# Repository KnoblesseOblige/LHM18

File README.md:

# LHM18 Keyboard

  This is a Left Hand Mini 1800 style keyboard that was my first project to learn PCB design through KiCAD. The PCB design is based around a ProMicro and daughter board which uses USB mini-B similar to the [Tanuki Keyboard](https://github.com/SethSenpai/Tanuki). The PCB only supports the layout that is shown in the image above. Please feel free to modify the PCB or case files to fit your needs. 

 # Case

 The case is a typical top mounted desin with the intention for it to be 3D printed with the mounting solution being M2 heat-set inserts and screws. I sourced my hardware from McMaster-Carr:

 [M2 Heat-Set Insert](https://www.mcmaster.com/94180a307) qty 10

 [M2 Screws](https://www.mcmaster.com/92000a012) qty 10

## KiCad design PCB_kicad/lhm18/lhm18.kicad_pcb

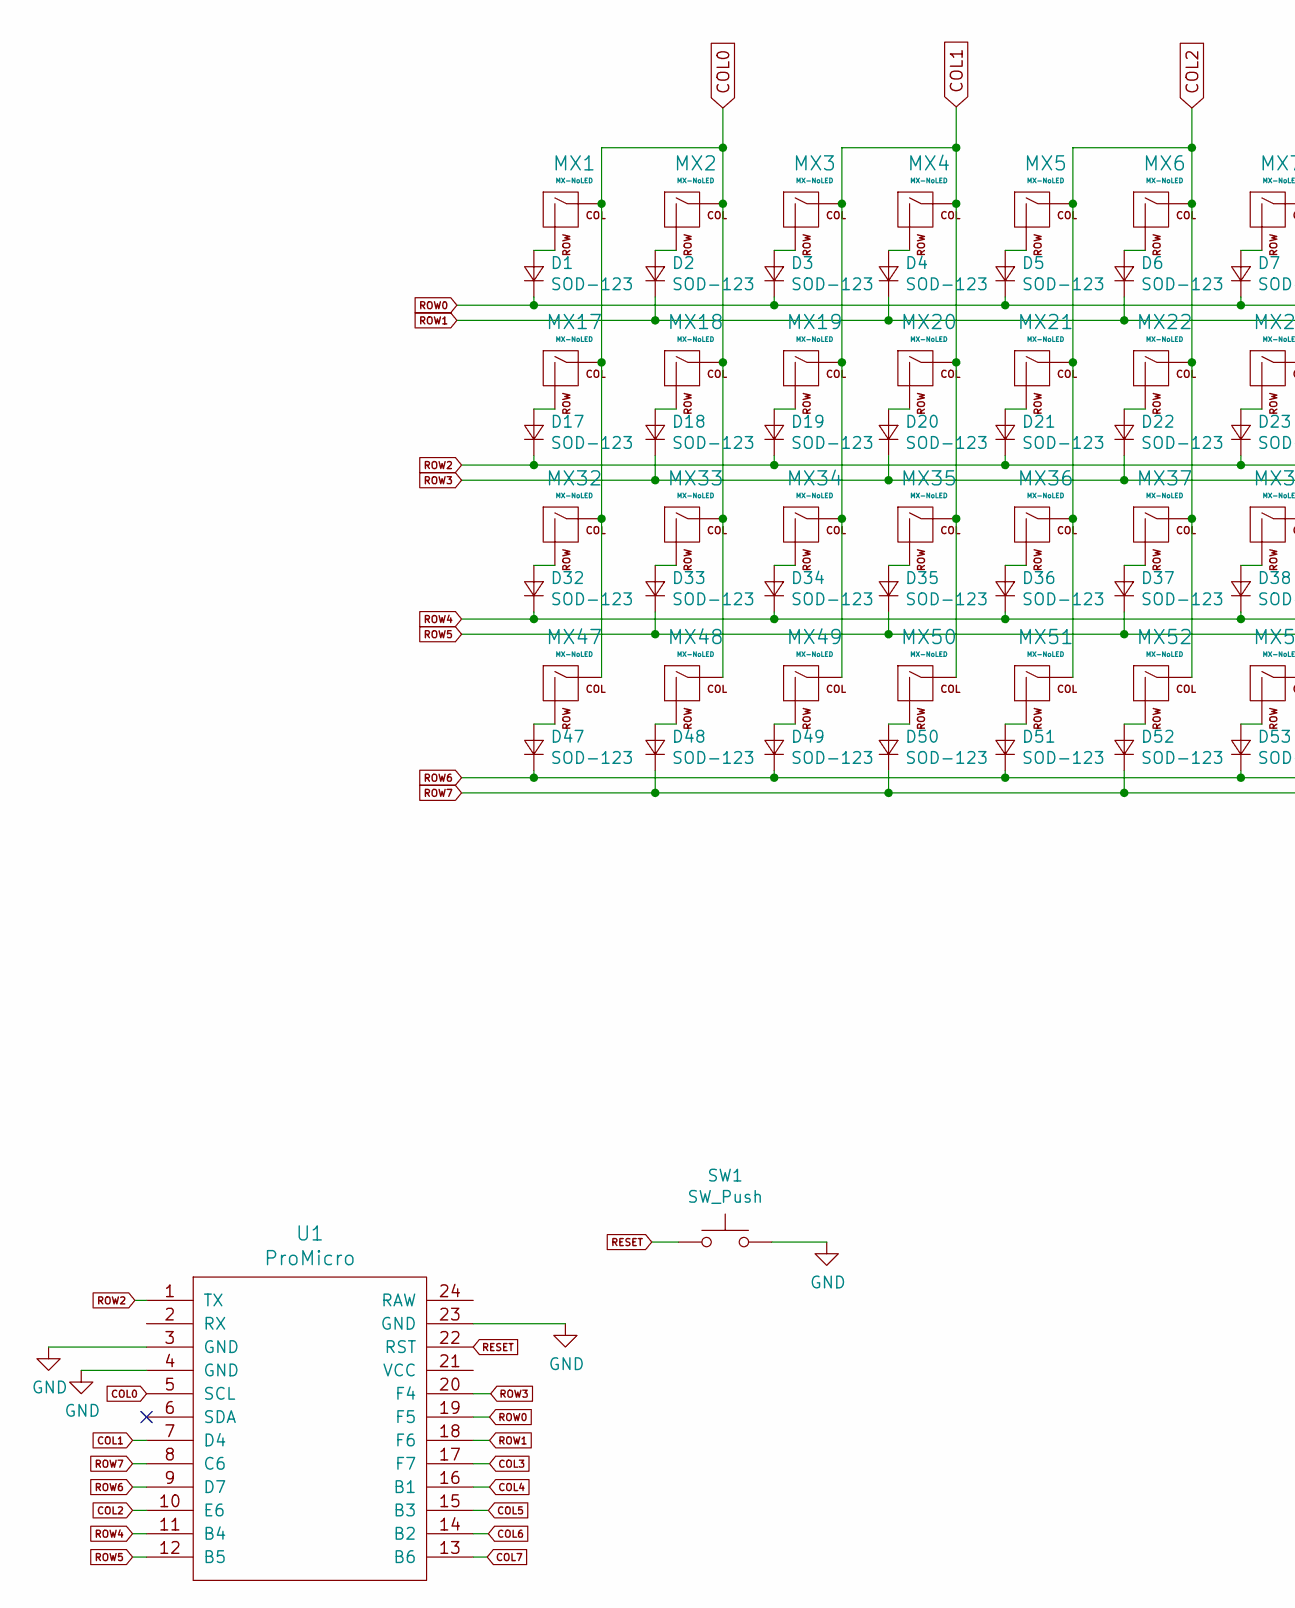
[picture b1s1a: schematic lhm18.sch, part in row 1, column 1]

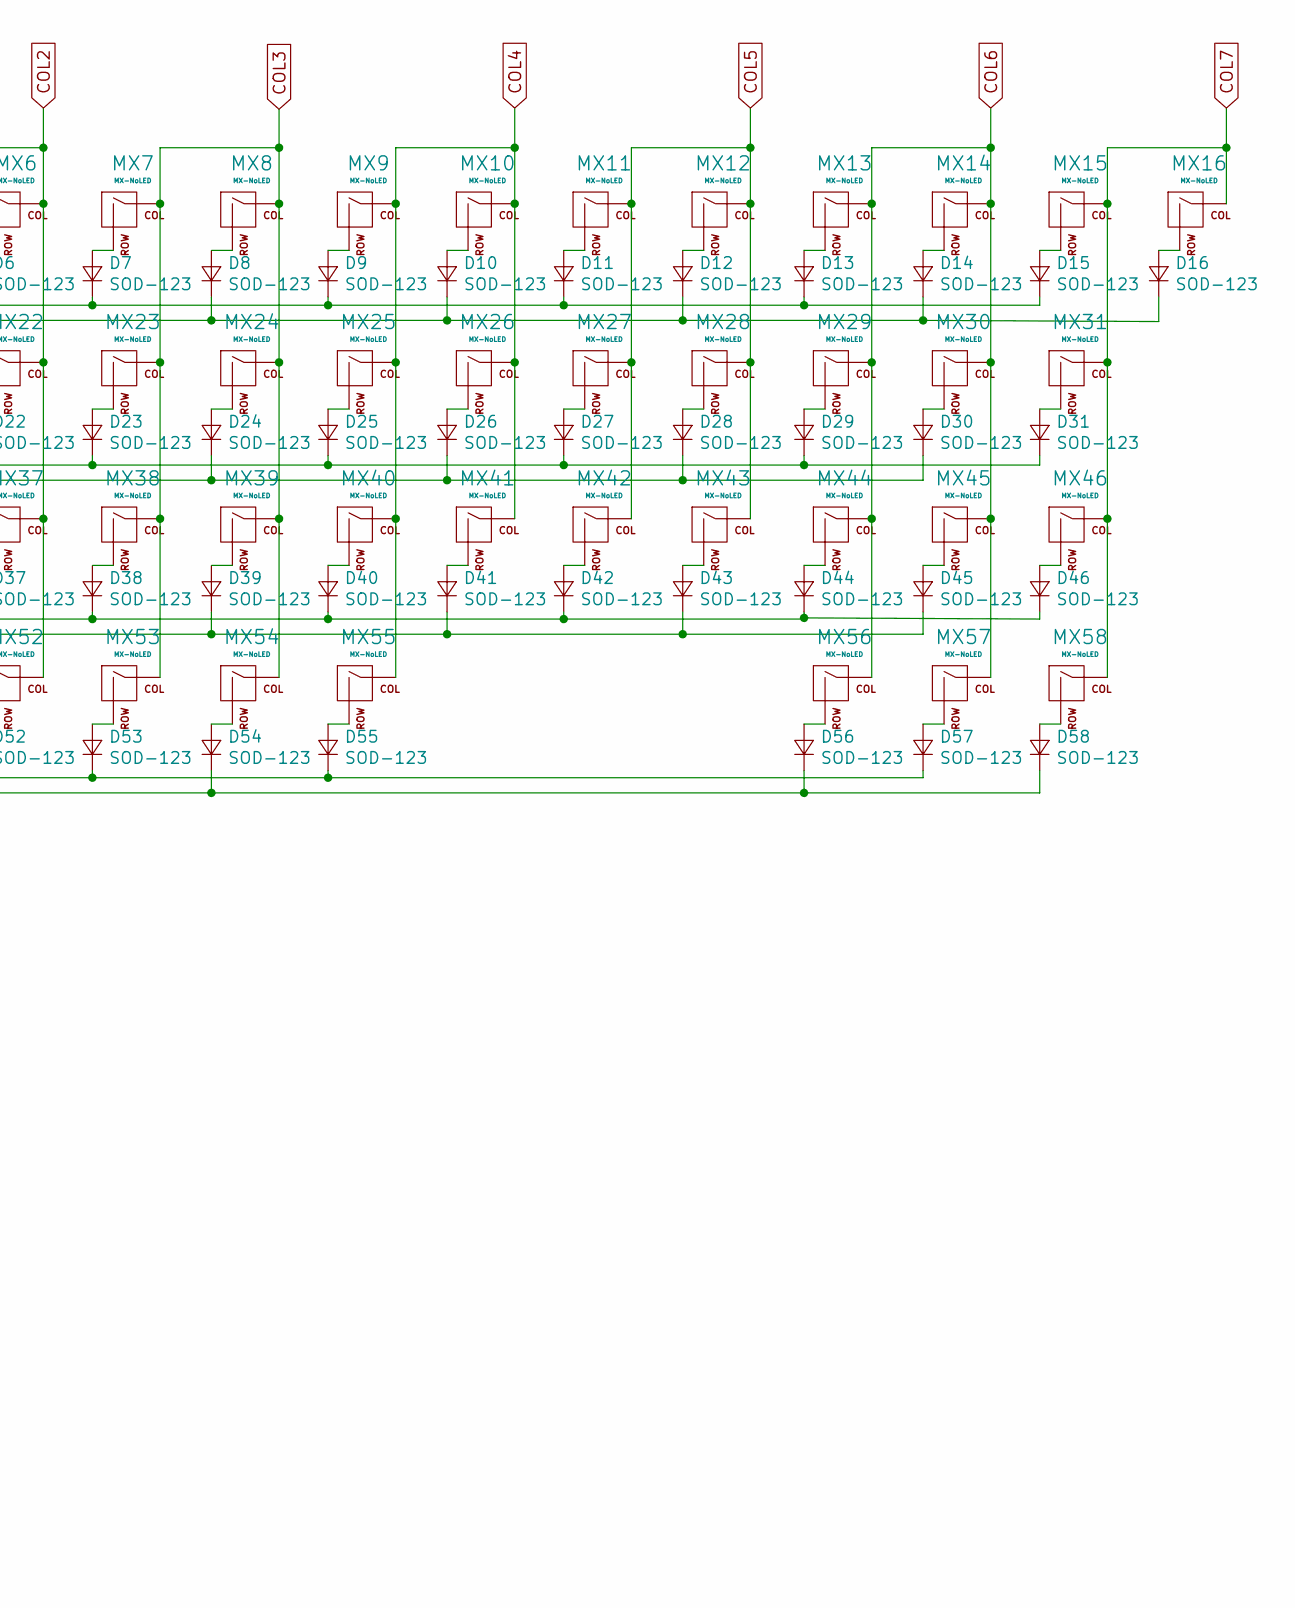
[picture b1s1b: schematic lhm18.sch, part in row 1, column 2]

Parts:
D1, D2, D3, D4, D5, D6, D7, D8, D9, D10, D11, D12, D13, D14, D15, D16, D17, D18, D19, D20, D21, D22, D23, D24, D25, D26, D27, D28, D29, D30, D31, D32, D33, D34, D35, D36, D37, D38, D39, D40, D41, D42, D43, D44, D45, D46, D47, D48, D49, D50, D51, D52, D53, D54, D55, D56, D57, D58: SOD-123; D_SOD123_axial
MX1, MX2, MX3, MX4, MX5, MX6, MX7, MX8, MX9, MX10, MX11, MX12, MX13, MX14, MX15, MX16, MX17, MX18, MX19, MX20, MX22, MX23, MX24, MX25, MX26, MX27, MX28, MX29, MX30, MX32, MX33, MX34, MX35, MX37, MX38, MX39, MX40, MX41, MX42, MX43, MX44, MX45, MX47, MX48, MX49, MX50, MX51, MX57: MX-NoLED; MXOnly-1U-NoLED
MX21, MX46, MX52, MX53, MX56, MX58: MX-NoLED; MXOnly-1.25U-NoLED
MX31, MX36: MX-NoLED; MXOnly-1.75U-NoLED
MX54: MX-NoLED; MXOnly-2.25U-ReversedStabilizers-NoLED
MX55: MX-NoLED; MXOnly-2.75U-ReversedStabilizers-NoLED
SW1: SW_Push; SKQG-1155865
U1: ProMicro

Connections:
COL0: MX1.1 (COL), MX2.1 (COL), MX17.1 (COL), MX18.1 (COL), MX32.1 (COL), MX33.1 (COL), MX47.1 (COL), MX48.1 (COL), U1.5 (SCL)
COL1: MX3.1 (COL), MX4.1 (COL), MX19.1 (COL), MX20.1 (COL), MX34.1 (COL), MX35.1 (COL), MX49.1 (COL), MX50.1 (COL), U1.7 (D4)
COL2: MX5.1 (COL), MX6.1 (COL), MX21.1 (COL), MX22.1 (COL), MX36.1 (COL), MX37.1 (COL), MX51.1 (COL), MX52.1 (COL), U1.10 (E6)
COL3: MX7.1 (COL), MX8.1 (COL), MX23.1 (COL), MX24.1 (COL), MX38.1 (COL), MX39.1 (COL), MX53.1 (COL), MX54.1 (COL), U1.17 (F7)
COL4: MX9.1 (COL), MX10.1 (COL), MX25.1 (COL), MX26.1 (COL), MX40.1 (COL), MX41.1 (COL), MX55.1 (COL), U1.16 (B1)
COL5: MX11.1 (COL), MX12.1 (COL), MX27.1 (COL), MX28.1 (COL), MX42.1 (COL), MX43.1 (COL), U1.15 (B3)
COL6: MX13.1 (COL), MX14.1 (COL), MX29.1 (COL), MX30.1 (COL), MX44.1 (COL), MX45.1 (COL), MX56.1 (COL), MX57.1 (COL), U1.14 (B2)
COL7: MX15.1 (COL), MX16.1 (COL), MX31.1 (COL), MX46.1 (COL), MX58.1 (COL), U1.13 (B6)
GND: SW1.2, U1.3 (GND), U1.4 (GND), U1.23 (GND)
unnamed: D1.2 (A), MX1.2 (ROW)
unnamed: D2.2 (A), MX2.2 (ROW)
unnamed: D3.2 (A), MX3.2 (ROW)
unnamed: D4.2 (A), MX4.2 (ROW)
unnamed: D5.2 (A), MX5.2 (ROW)
unnamed: D6.2 (A), MX6.2 (ROW)
unnamed: D7.2 (A), MX7.2 (ROW)
unnamed: D8.2 (A), MX8.2 (ROW)
unnamed: D9.2 (A), MX9.2 (ROW)
unnamed: D10.2 (A), MX10.2 (ROW)
unnamed: D11.2 (A), MX11.2 (ROW)
unnamed: D12.2 (A), MX12.2 (ROW)
unnamed: D13.2 (A), MX13.2 (ROW)
unnamed: D14.2 (A), MX14.2 (ROW)
unnamed: D15.2 (A), MX15.2 (ROW)
unnamed: D16.2 (A), MX16.2 (ROW)
unnamed: D17.2 (A), MX17.2 (ROW)
unnamed: D18.2 (A), MX18.2 (ROW)
unnamed: D19.2 (A), MX19.2 (ROW)
unnamed: D20.2 (A), MX20.2 (ROW)
unnamed: D21.2 (A), MX21.2 (ROW)
unnamed: D22.2 (A), MX22.2 (ROW)
unnamed: D23.2 (A), MX23.2 (ROW)
unnamed: D24.2 (A), MX24.2 (ROW)
unnamed: D25.2 (A), MX25.2 (ROW)
unnamed: D26.2 (A), MX26.2 (ROW)
unnamed: D27.2 (A), MX27.2 (ROW)
unnamed: D28.2 (A), MX28.2 (ROW)
unnamed: D29.2 (A), MX29.2 (ROW)
unnamed: D30.2 (A), MX30.2 (ROW)
unnamed: D31.2 (A), MX31.2 (ROW)
unnamed: D32.2 (A), MX32.2 (ROW)
unnamed: D33.2 (A), MX33.2 (ROW)
unnamed: D34.2 (A), MX34.2 (ROW)
unnamed: D35.2 (A), MX35.2 (ROW)
unnamed: D36.2 (A), MX36.2 (ROW)
unnamed: D37.2 (A), MX37.2 (ROW)
unnamed: D38.2 (A), MX38.2 (ROW)
unnamed: D39.2 (A), MX39.2 (ROW)
unnamed: D40.2 (A), MX40.2 (ROW)
unnamed: D41.2 (A), MX41.2 (ROW)
unnamed: D42.2 (A), MX42.2 (ROW)
unnamed: D43.2 (A), MX43.2 (ROW)
unnamed: D44.2 (A), MX44.2 (ROW)
unnamed: D45.2 (A), MX45.2 (ROW)
unnamed: D46.2 (A), MX46.2 (ROW)
unnamed: D47.2 (A), MX47.2 (ROW)
unnamed: D48.2 (A), MX48.2 (ROW)
unnamed: D49.2 (A), MX49.2 (ROW)
unnamed: D50.2 (A), MX50.2 (ROW)
unnamed: D51.2 (A), MX51.2 (ROW)
unnamed: D52.2 (A), MX52.2 (ROW)
unnamed: D53.2 (A), MX53.2 (ROW)
unnamed: D54.2 (A), MX54.2 (ROW)
unnamed: D55.2 (A), MX55.2 (ROW)
unnamed: D56.2 (A), MX56.2 (ROW)
unnamed: D57.2 (A), MX57.2 (ROW)
unnamed: D58.2 (A), MX58.2 (ROW)
RESET: SW1.1, U1.22 (RST)
RGB: U1.2 (RX)
ROW0: D1.1 (K), D3.1 (K), D5.1 (K), D7.1 (K), D9.1 (K), D11.1 (K), D13.1 (K), D15.1 (K), U1.19 (F5)
ROW1: D2.1 (K), D4.1 (K), D6.1 (K), D8.1 (K), D10.1 (K), D12.1 (K), D14.1 (K), D16.1 (K), U1.18 (F6)
ROW2: D17.1 (K), D19.1 (K), D21.1 (K), D23.1 (K), D25.1 (K), D27.1 (K), D29.1 (K), D31.1 (K), U1.1 (TX)
ROW3: D18.1 (K), D20.1 (K), D22.1 (K), D24.1 (K), D26.1 (K), D28.1 (K), D30.1 (K), U1.20 (F4)
ROW4: D32.1 (K), D34.1 (K), D36.1 (K), D38.1 (K), D40.1 (K), D42.1 (K), D44.1 (K), D46.1 (K), U1.11 (B4)
ROW5: D33.1 (K), D35.1 (K), D37.1 (K), D39.1 (K), D41.1 (K), D43.1 (K), D45.1 (K), U1.12 (B5)
ROW6: D47.1 (K), D49.1 (K), D51.1 (K), D53.1 (K), D55.1 (K), D57.1 (K), U1.9 (D7)
ROW7: D48.1 (K), D50.1 (K), D52.1 (K), D54.1 (K), D56.1 (K), D58.1 (K), U1.8 (C6)
VCC: U1.21 (VCC)

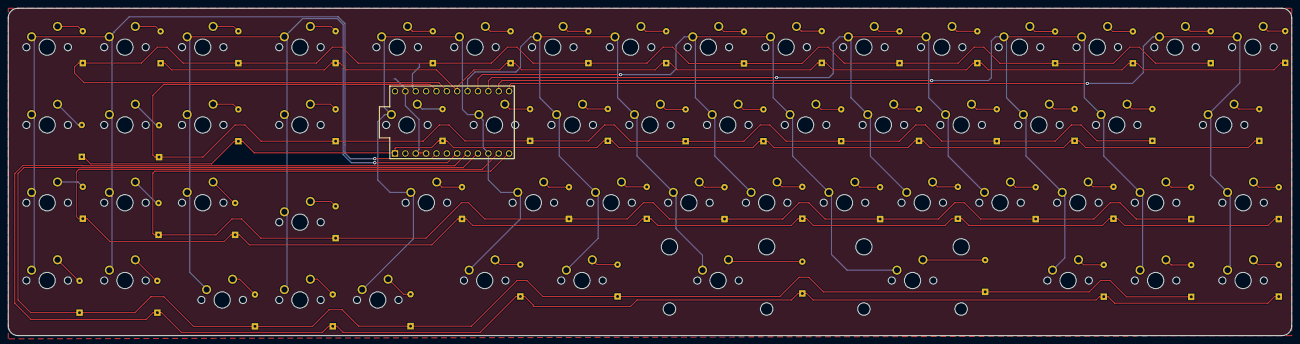
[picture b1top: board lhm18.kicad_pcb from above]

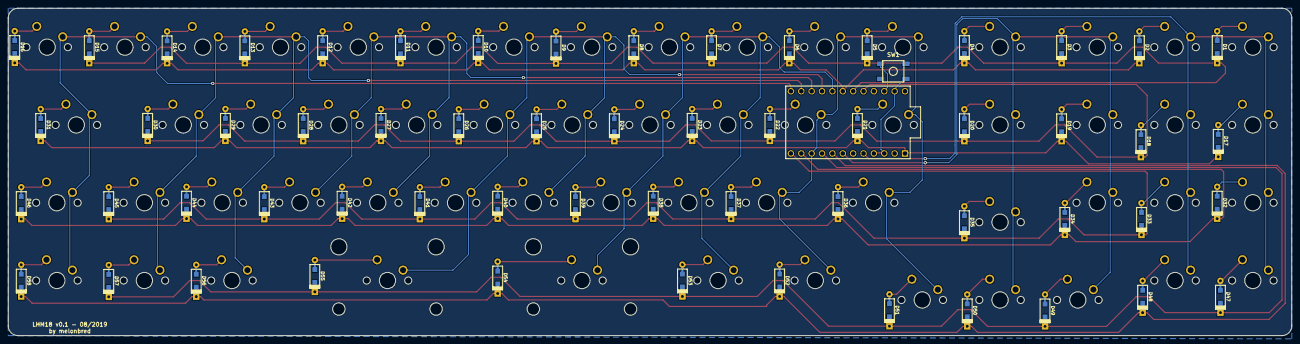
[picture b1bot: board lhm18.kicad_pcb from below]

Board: 2 copper layers, 314.3 x 80.2 mm, 118 parts (59 on the bottom side), 76 nets.
